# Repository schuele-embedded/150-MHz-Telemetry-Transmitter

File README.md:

# 150-MHz-Telemetry-Transmitter
Ultra Low Power VHF-Transmitter for Wildlife Radio Tagging

This Transmitter is an adaption of http://http://people.ece.cornell.edu/land/PROJECTS/TRANSMIT/.<br>
It has some minor changes and uses only discrete components as winding all coils etc. manually needs a lot of experienece, luck and effort to get the circuit running well and robust, which I hardly had to experience...
I got two versions running stable, one manufactured in THT and one in SMD.

This circuit allows to build a low-cost, tiny, light weight and very low power VHF-pulse-transmitter from scratch.
It's purpose is to be used in scientific tracking applications for wildlife and livestock.
This is the easiest but most effective transmitter circuit which is known to me.

This circuit is operating on 150 MHz and as all radio transmitters also emitting electromagnetic waves at harmonic frequencies, so be sure that you now your local rules for the emitted frequency spectrum! This report is only a theoretical abstract so there is no legal  warranty.

This circuit is based on developments in the early 70s on radio telemetry for wildlife and still base for many transmitters nowadays.
Check also R. Kenwards book "A manual for wildlife radio tagging" if you're interested in further information and advanced knowledge in radio tagging.

The circuit is in principle a very simple single-stage oscillator based on the third harmonic of a 50MHz crystal (you can also use a different frequency crystal). Its emitting short pulses of a continuous wave signal.
The pulse width and pulsing frequency is determined by a simple RC-network. 
This transmitter can also be used for simple data modulation using ASK (Amplitude Shift Keying) with On-Off-Keying (OOK) by removing the components Rp and Rc and turning on/off the oscillator by applying/removing voltage (with levels Uin/GND) directly to resistor R1 (Node "EN").

Best results were found with the following values:

C1 = 100 nF<br>
L1 = 100 nH (In THT wind copper coil: 4x0.4mm, diameter 3mm)<br>
R1 = 390 kOhm<br>
C2 = 15 pF<br>
L2 = 1 µH (In THT wind copper coil: 12x0.4mm, diameter 3mm)<br>
NPN = MMBT3904 (In THT: 2N3904)<br>
XTAL = 50 MHz<br>
3rd harmonic determines transmitter frequency<br>

Rp = 0-1 MOhm<br>
Cp = 0-5 µF<br>
Combination of Rp and Cp determine the pulse width and Pulsing frequency.

This circuit can be build on a small pcb (see also eagle schematic and layout in ".../eagle/") or directly solder the THT components to each other as a "flying assembly".
As antenna you can use just a piece of copper wire with length lambda/4 which is for 150MHz: 2m/4 = 50 cm

The PCB SMD version got an additional matching capacitor Cm with value 2.2pF which was added in series to the antenna.

Some characterization results:

The supply voltage can be as low as 0.7V and the circuit consumes only 1.5 mA @ 2.5V.
A simple, small, light coin cell with 1.5V for example can be used as power supply.

Maximum datarate is 250 baud with ASK/OOK modulation.

This graph shows the relative emitted power at harmonic frequencies and the narrow signal at 150 MHz.

As receiver a very low cost china handheld device Baofeng UV-5R (30€) was used and a Telonics RA-14 H-antenna which is matched to 150 MHz. 

With this setup a maximum distance through forest was found at even 350m.

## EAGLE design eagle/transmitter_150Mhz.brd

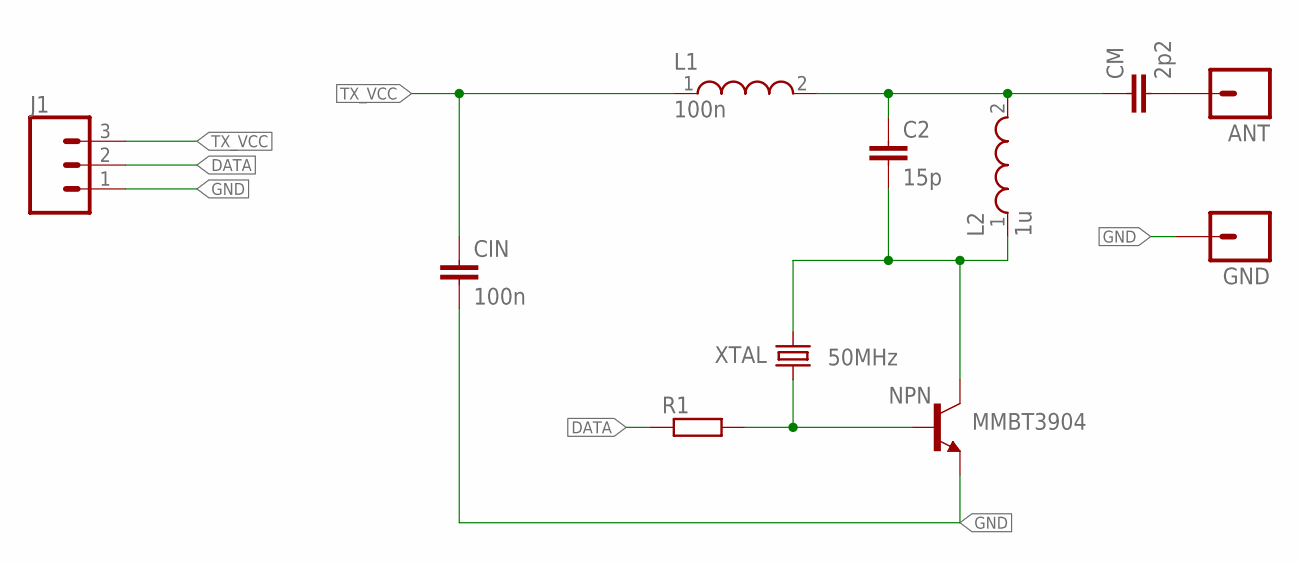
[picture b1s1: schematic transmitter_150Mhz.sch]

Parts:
ANT: M01OFFSET; 1X01_OFFSET
C2: 15p; C0603
CIN: 100n; C0603
CM: 2p2; C0603
GND: M01OFFSET; 1X01_OFFSET
J1: CONN_03; 1X03
L1: 100n; WE-PMI_0805
L2: 1u; WE-PMI_0806
NPN: MMBT3904; SOT23-BEC
R1: R-EU_R0603; R0603
XTAL: 50MHz; SM49

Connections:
ANT: C2.1, CM.1, L1.2, L2.2
DATA: J1.2, R1.1
GND: CIN.2, GND.1, J1.1, NPN.E
unnamed: ANT.1, CM.2
unnamed: NPN.B, R1.2, XTAL.1
unnamed: C2.2, L2.1, NPN.C, XTAL.2
TX_VCC: CIN.1, J1.3, L1.1

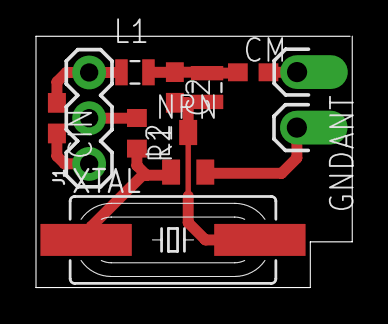
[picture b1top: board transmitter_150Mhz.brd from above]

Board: 2 copper layers, 17.6 x 14.0 mm, 11 parts (0 on the bottom side), 7 nets.

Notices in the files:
parts and their libraries:
SparkFun-Connectors: Licensing: Creative Commons ShareAlike 4.0 International - https://creativecommons.org/licenses/by-sa/4.0
Wurth_Elektronik_Passive_rev15b: Copyright: Würth Elektronik
